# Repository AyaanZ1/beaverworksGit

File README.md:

# beaverworksGit

A maze-navigating robot built around an Arduino Mega 2560, combining custom
PCB design (KiCad) with firmware for grid-based autonomous navigation,
sensor logging, and ESP32-CAM video streaming.

## Overview

The robot drives through a 5x5 grid maze along a pre-defined path, correcting
its heading with an IMU (gyro yaw tracking) instead of relying on open-loop
timing alone. At each cell it pauses to read temperature, humidity, and
distance-to-obstacle, then reports the data back over serial. A light sensor
and buzzer provide simple flashlight/alarm behavior along the way, and a
separate ESP32-CAM module streams live video.

## Repository Structure

```
.
├── beaverworksGit.kicad_pro/.kicad_sch/.kicad_pcb  # KiCad project (schematic + PCB layout)
├── fp-lib-table                                    # KiCad footprint library table
├── hardware/                                        # Hardware design files
│   ├── beaverworksGit.kicad_*                       #   (duplicate/working copy of the KiCad project)
│   ├── Arduino Mega 2560 Rev3 A000067/               #   Arduino Mega 3D model + footprint
│   ├── Arduino_MountingHole.pretty/                  #   Mounting hole footprints
│   ├── HC-SR04 Model by SparkFun/                    #   Ultrasonic sensor 3D model + footprint
│   └── esp32-wrover-kicad-master/                    #   ESP32-WROVER KiCad library (third-party)
├── software/                                        # Firmware / companion scripts
│   ├── IMU Navigation/
│   │   ├── ObstacleAvoidance.ino                     #   Standalone obstacle-avoidance sketch
│   │   ├── Calibration/calibration.ino                #   IMU/gyro calibration routine
│   │   └── Yaw Tracking/mpu6050_copy_*/               #   MPU6050 yaw-tracking test sketch
│   ├── ESP32_Camera/                                 #   ESP32-CAM web server + streaming
│   │   ├── CameraWebServer.ino                        #     Main camera sketch (based on Espressif's CameraWebServer example)
│   │   ├── app_httpd.cpp / camera_pins.h / ...         #     Supporting camera server code
│   │   ├── wifi_secrets.example.h                     #     Template for Wi-Fi credentials (copy to wifi_secrets.h)
│   │   ├── record_video.py / stream_test.py            #     Python helpers for grabbing/testing the video stream
│   │   └── python/                                     #     Additional Python utilities
│   └── Sensors_Code/                                 #   (sensor test code)
├── main.cpp                                          # Main robot firmware: timed turns/drives, no gyro
├── navigatio.cpp                                     # Main robot firmware: gyro-corrected turns/drives (MPU6050)
└── platformio.ini                                    # PlatformIO project config (Arduino Mega target)
```

## Hardware

- **MCU:** Arduino Mega 2560 Rev3
- **IMU:** Adafruit MPU6050 (gyro-based yaw tracking)
- **Distance sensing:** HC-SR04 ultrasonic sensor
- **Environmental sensing:** DHT11 temperature/humidity sensor
- **Other I/O:** LDR (light sensor), sound sensor, buzzer, status LED
- **Drive:** Dual DC motors via an H-bridge driver (enable + direction pins per side)
- **Camera:** Separate ESP32-CAM module for live video streaming
- **PCB:** Custom board designed in KiCad (see `beaverworksGit.kicad_pro` / `hardware/`)

## Firmware

There are two versions of the main navigation firmware:

| File | Description |
|---|---|
| `main.cpp` | Drives a fixed sequence of grid moves using timed turns and timed straight-line driving (open-loop, no IMU feedback). |
| `navigatio.cpp` | Same grid path, but uses the MPU6050 gyro to track yaw in real time and correct heading while turning and driving (closed-loop). |

Both firmware versions:
1. Follow a hard-coded `path[]` array of `NORTH`/`EAST`/`SOUTH`/`WEST` moves through a 5x5 grid.
2. Stop at each cell to read temperature, humidity, and ultrasonic distance, and report them over serial.
3. Continuously monitor light and sound sensors to trigger an LED "flashlight" and buzzer alert.
4. Stop and idle once the path is complete.

### Building with PlatformIO

The project is set up for [PlatformIO](https://platformio.org/) targeting the Arduino Mega:

```bash
# Build
pio run

# Upload to the board
pio run -t upload

# Open the serial monitor (9600 baud)
pio device monitor
```

Dependencies (declared in `platformio.ini`):
- `adafruit/Adafruit MPU6050`
- `adafruit/Adafruit Unified Sensor`
- `adafruit/DHT sensor library`

> Note: only one of `main.cpp` / `navigatio.cpp` should be treated as the active
> `src/main.cpp` for a given build — move/copy whichever version you want to
> flash into PlatformIO's `src/` directory (or update `platformio.ini`'s
> `build_src_filter` accordingly).

### ESP32-CAM streaming

`software/ESP32_Camera/CameraWebServer.ino` is based on the standard Espressif
CameraWebServer example, adapted with local board/pin config. To use it:

1. Copy `wifi_secrets.example.h` to `wifi_secrets.h` and fill in your Wi-Fi
   SSID and password.
2. Flash `CameraWebServer.ino` to an ESP32-CAM board via the Arduino IDE
   (select the correct board and partition scheme — see `partitions.csv`).
3. Use `stream_test.py` or `record_video.py` to test/capture the resulting
   MJPEG stream from a computer on the same network.

### IMU navigation experiments

`software/IMU Navigation/` contains standalone sketches used during
development:
- `Calibration/calibration.ino` — computes gyro bias for the MPU6050.
- `Yaw Tracking/mpu6050_copy_*/` — isolated yaw-tracking test.
- `ObstacleAvoidance.ino` — simple reactive obstacle-avoidance behavior.

## Hardware Design (KiCad)

Open `beaverworksGit.kicad_pro` in [KiCad](https://www.kicad.org/) to view or
edit the schematic (`.kicad_sch`) and PCB layout (`.kicad_pcb`). Third-party
footprints/3D models used in the design are vendored under `hardware/`
(Arduino Mega, HC-SR04, ESP32-WROVER, mounting holes).

## Status

This is a work-in-progress class/competition project (Beaverworks). Firmware
constants such as `MS_PER_INCH`, `MS_PER_90_TURN`, drive speeds, and the
maze `path[]` are tuned for a specific physical maze layout and will need
recalibrating for a different course or robot chassis.

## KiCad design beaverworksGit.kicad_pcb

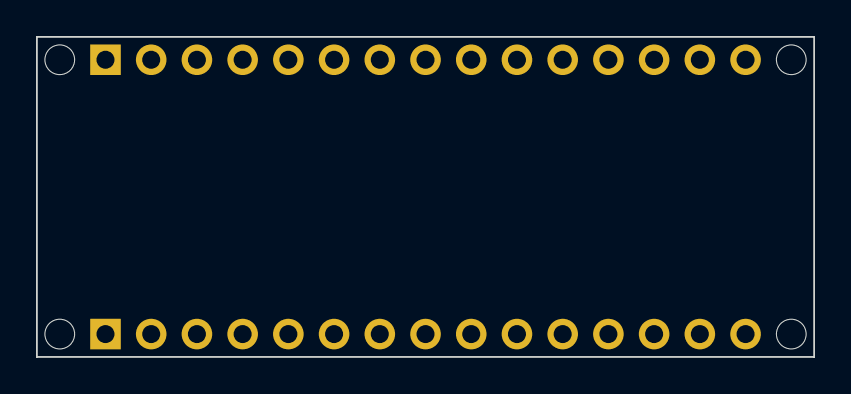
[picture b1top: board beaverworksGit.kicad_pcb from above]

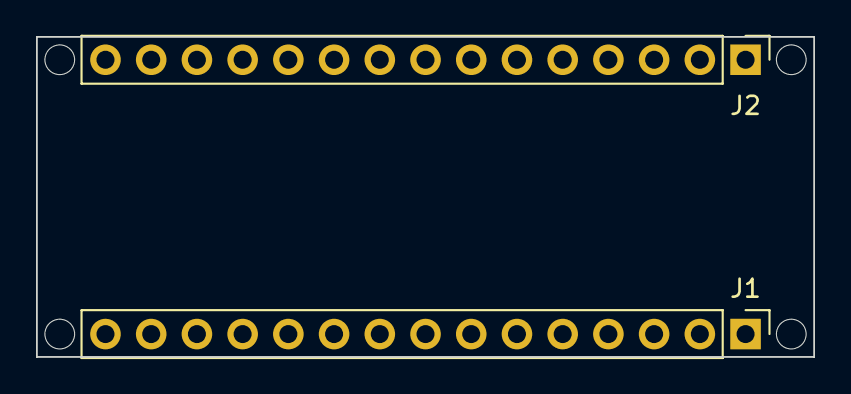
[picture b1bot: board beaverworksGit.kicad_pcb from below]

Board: 2 copper layers, 43.2 x 17.8 mm, 6 parts (2 on the bottom side), 2 nets, no tracks yet.

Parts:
J1: Analog; PinHeader_1x15_P2.54mm_Vertical
J2: Digital; PinHeader_1x15_P2.54mm_Vertical
MH1, MH2, MH3, MH4: MountingHole_65mil

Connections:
/~RESET: J1.13, J2.13
GND: J1.14, J2.12
